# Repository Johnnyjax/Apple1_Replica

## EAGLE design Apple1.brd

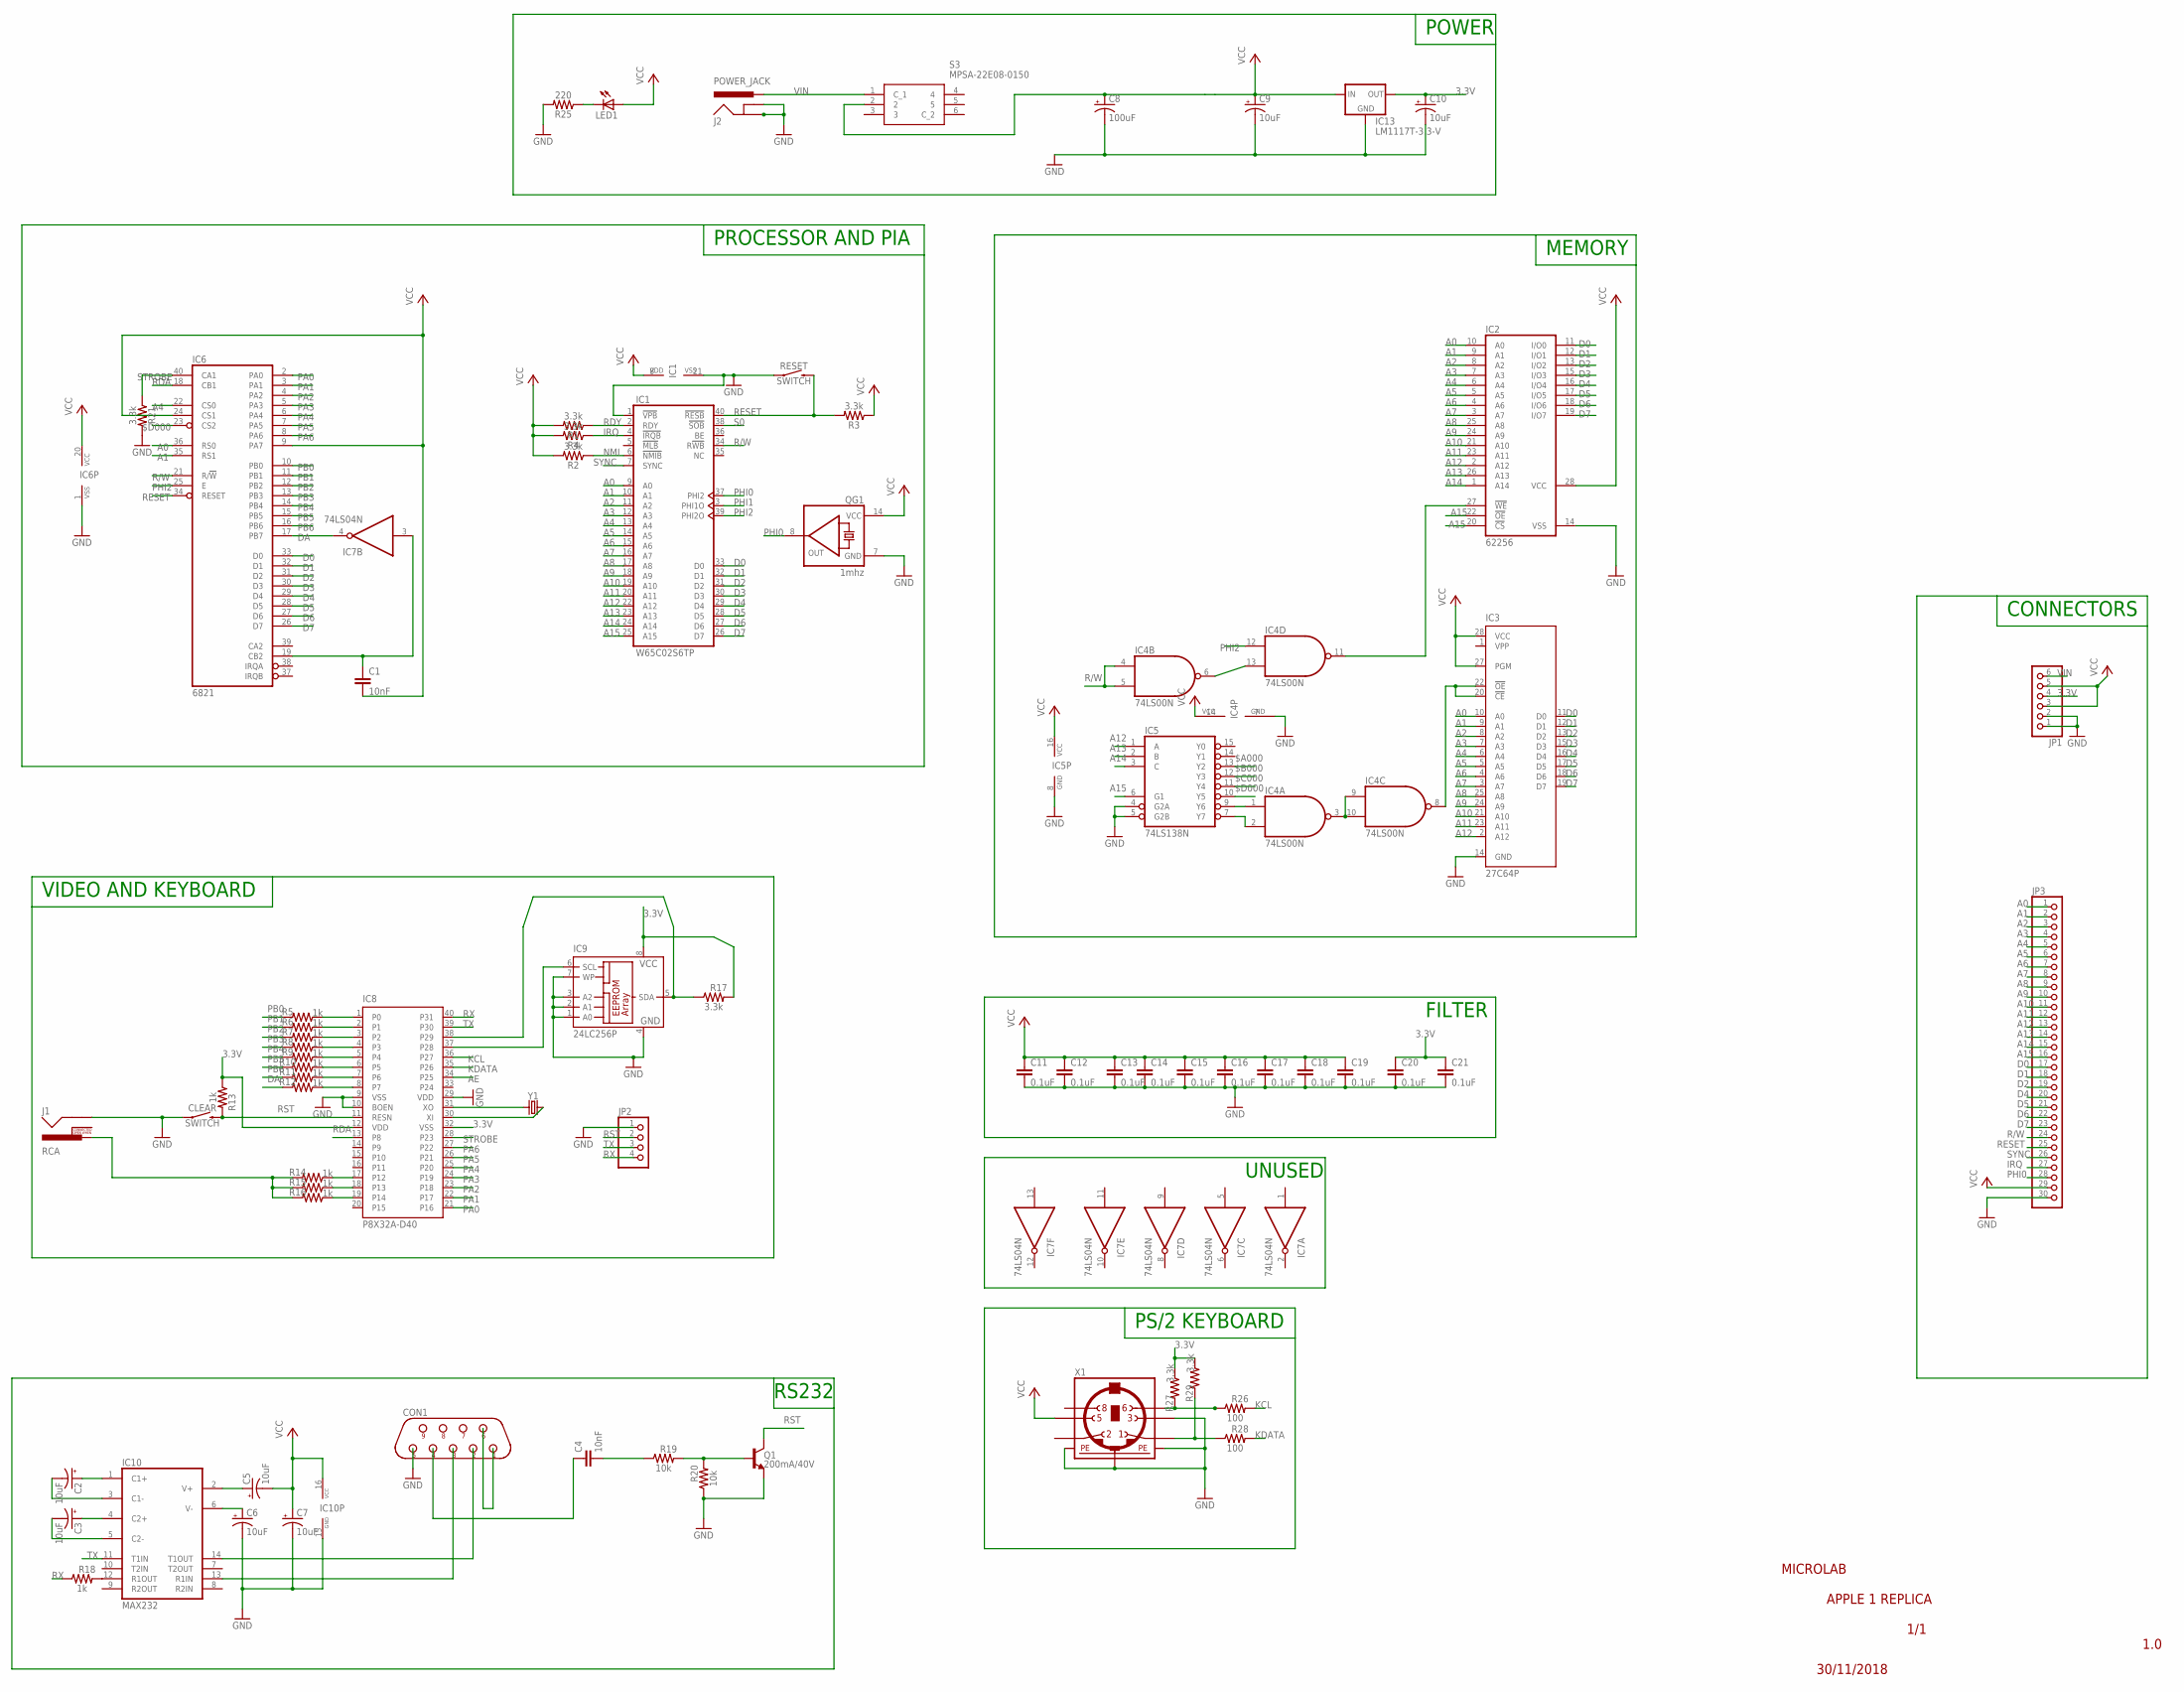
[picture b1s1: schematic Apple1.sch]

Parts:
C1, C4: 10nF; CAP-PTH-10MM
C2, C3, C5, C6, C7, C9, C10: 10uF; CPOL-RADIAL-2.5MM-5MM
C8: 100uF; CPOL-RADIAL-2.5MM-6.5MM
C11, C12, C13, C14, C15, C16, C17, C18, C19, C20, C21: 0.1uF; CAP-PTH-SMALL-KIT
CLEAR: SWITCH; TACTILE_SWITCH_PTH_6.0MM
CON1: DB9F; D-09F
IC1: W65C02S6TP; DIL40
IC2: 62256; DIL28-6
IC3: 27C64P; DIL28-6
IC4: 74LS00N; DIL14
IC5: 74LS138N; DIL16
IC6: 6821; DIL40
IC7: 74LS04N; DIL14
IC8: P8X32A-D40; DIL40
IC9: 24LC256P; DIL8
IC10: MAX232; DIL16
IC13: LM1117T-3.3-V; TO220V
J1: RCA
J2: POWER_JACK; POWER_JACK_PTH
JP1: PINHD-1X6B; 1X06-BIG
JP2: PINHD-1X4; 1X04
JP3: PINHD-1X30; 1X30
LED1: LED5MM
Q1: 200mA/40V; TO-92
QG1: 1mhz; DIL14S
R1, R2, R3, R4, R17, R21, R27, R29: 3.3k; AXIAL-0.3
R5, R6, R7, R8, R9, R10, R11, R12, R13, R14, R15, R16, R18: 1k; AXIAL-0.3
R19, R20: 10k; AXIAL-0.3
R25: 220; AXIAL-0.3
R26, R28: 100; AXIAL-0.3
RESET: SWITCH; TACTILE_SWITCH_PTH_6.0MM
S3: MPSA-22E08-0150; MPSA22E080150
X1: MINI_DIN_6; M_DIN6
Y1: CRYSTALPTH-HC49UV; HC49U

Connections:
3.3V: C10.1 (+), C20.1, C21.1, IC8.12 (VDD), IC8.32 (VSS), IC9.8 (VCC), IC13.2 (OUT), JP1.4, R13.P$1 (1), R17.P$2 (2), R27.P$1 (1), R29.P$1 (1)
$A000: IC5.13 (Y2)
$B000: IC5.12 (Y3)
$C000: IC5.11 (Y4)
$D000: IC5.10 (Y5), IC6.23 (CS2)
A0: IC1.9 (A0), IC2.10 (A0), IC3.10 (A0), IC6.36 (RS0), JP3.1
A1: IC1.10 (A1), IC2.9 (A1), IC3.9 (A1), IC6.35 (RS1), JP3.2
A2: IC1.11 (A2), IC2.8 (A2), IC3.8 (A2), JP3.3
A3: IC1.12 (A3), IC2.7 (A3), IC3.7 (A3), JP3.4
A4: IC1.13 (A4), IC2.6 (A4), IC3.6 (A4), IC6.22 (CS0), JP3.5
A5: IC1.14 (A5), IC2.5 (A5), IC3.5 (A5), JP3.6
A6: IC1.15 (A6), IC2.4 (A6), IC3.4 (A6), JP3.7
A7: IC1.16 (A7), IC2.3 (A7), IC3.3 (A7), JP3.8
A8: IC1.17 (A8), IC2.25 (A8), IC3.25 (A8), JP3.9
A9: IC1.18 (A9), IC2.24 (A9), IC3.24 (A9), JP3.10
A10: IC1.19 (A10), IC2.21 (A10), IC3.21 (A10), JP3.11
A11: IC1.20 (A11), IC2.23 (A11), IC3.23 (A11), JP3.12
A12: IC1.22 (A12), IC2.2 (A12), IC3.2 (A12), IC5.1 (A), JP3.13
A13: IC1.23 (A13), IC2.26 (A13), IC5.2 (B), JP3.14
A14: IC1.24 (A14), IC2.1 (A14), IC5.3 (C), JP3.15
A15: IC1.25 (A15), IC2.20 (!CS), IC2.22 (!OE), IC5.6 (G1), JP3.16
AE: IC8.34 (P25)
D0: IC1.33 (D0), IC2.11 (I/O0), IC3.11 (D0), IC6.33 (D0), JP3.17
D1: IC1.32 (D1), IC2.12 (I/O1), IC3.12 (D1), IC6.32 (D1), JP3.18
D2: IC1.31 (D2), IC2.13 (I/O2), IC3.13 (D2), IC6.31 (D2), JP3.19
D3: IC1.30 (D3), IC2.15 (I/O3), IC3.15 (D3), IC6.30 (D3)
D4: IC1.29 (D4), IC2.16 (I/O4), IC3.16 (D4), IC6.29 (D4), JP3.20
D5: IC1.28 (D5), IC2.17 (I/O5), IC3.17 (D5), IC6.28 (D5), JP3.21
D6: IC1.27 (D6), IC2.18 (I/O6), IC3.18 (D6), IC6.27 (D6), JP3.22
D7: IC1.26 (D7), IC2.19 (I/O7), IC3.19 (D7), IC6.26 (D7), JP3.23
DA: IC6.17 (PB7), IC7.4 (O), R12.P$2 (2)
GND: C6.2 (-), C7.2 (-), C8.2 (-), C9.2 (-), C10.2 (-), C11.2, C12.2, C13.2, C14.2, C15.2, C16.2, C17.2, C18.2, C19.2, C20.2, C21.2, CLEAR.1, CON1.5, IC1.1 (!VPB), IC1.21 (VSS), IC2.14 (VSS), IC3.14 (GND), IC4.7 (GND), IC5.4 (G2A), IC5.5 (G2B), IC5.8 (GND), IC6.1 (VSS), IC7.7 (GND), IC8.9 (VSS), IC8.10 (BOEN), IC8.29 (VDD), IC9.1 (A0), IC9.2 (A1), IC9.3 (A2), IC9.4 (GND), IC9.7 (WP), IC10.15 (GND), IC13.1 (GND), J1.SHELL, J2.GND, J2.GNDBREAK, JP1.1, JP1.2, JP2.1, JP3.30, Q1.1 (E), QG1.7 (GND), R20.P$1 (1), R21.P$2 (2), R25.P$2 (2), RESET.1, X1.3, X1.SH1 (PE1), X1.SH2 (PE2), X1.SH3 (PE3)
IRQ: IC1.4 (!IRQB), JP3.27, R4.P$1 (1)
KCL: IC8.36 (P27), R26.P$2 (2)
KDATA: IC8.35 (P26), R28.P$2 (2)
unnamed: IC2.27 (!WE), IC4.11 (O)
unnamed: IC4.3 (O), IC4.9 (I0), IC4.10 (I1)
unnamed: IC3.20 (!CE), IC3.22 (!OE), IC4.8 (O)
unnamed: IC4.1 (I0), IC5.9 (Y6)
unnamed: IC4.2 (I1), IC5.7 (Y7)
unnamed: IC4.6 (O), IC4.13 (I1)
unnamed: C1.1, IC6.19 (CB2), IC7.3 (I)
unnamed: IC8.1 (P0), R5.P$1 (1)
unnamed: IC8.2 (P1), R6.P$1 (1)
unnamed: IC8.3 (P2), R7.P$1 (1)
unnamed: IC8.4 (P3), R8.P$1 (1)
unnamed: IC8.5 (P4), R9.P$1 (1)
unnamed: IC8.6 (P5), R10.P$1 (1)
unnamed: IC8.7 (P6), R11.P$1 (1)
unnamed: IC8.8 (P7), R12.P$1 (1)
unnamed: IC8.17 (P12), R14.P$1 (1)
unnamed: IC8.18 (P13), R15.P$1 (1)
unnamed: IC8.19 (P14), R16.P$1 (1)
unnamed: J1.PIN, R14.P$2 (2), R15.P$2 (2), R16.P$2 (2)
unnamed: IC8.31 (XO), Y1.1
unnamed: IC8.30 (XI), Y1.2
unnamed: IC10.12 (R1OUT), R18.P$2 (2)
unnamed: IC8.37 (P28), IC9.6 (SCL)
unnamed: IC8.38 (P29), IC9.5 (SDA), R17.P$1 (1)
unnamed: CON1.3, IC10.13 (R1IN)
unnamed: C2.1 (+), IC10.1 (C1+)
unnamed: C2.2 (-), IC10.3 (C1-)
unnamed: C3.1 (+), IC10.4 (C2+)
unnamed: C3.2 (-), IC10.5 (C2-)
unnamed: CON1.2, IC10.14 (T1OUT)
unnamed: CON1.1, CON1.6
unnamed: C4.1, CON1.4
unnamed: C4.2, R19.P$1 (1)
unnamed: Q1.2 (B), R19.P$2 (2), R20.P$2 (2)
unnamed: C5.1 (+), IC10.2 (V+)
unnamed: C6.1 (+), IC10.6 (V-)
unnamed: LED1.K (C), R25.P$1 (1)
unnamed: R26.P$1 (1), R27.P$2 (2), X1.6
unnamed: R28.P$1 (1), R29.P$2 (2), X1.1
NMI: IC1.6 (!NMIB), R2.P$1 (1)
PA0: IC6.2 (PA0), IC8.21 (P16)
PA1: IC6.3 (PA1), IC8.22 (P17)
PA2: IC6.4 (PA2), IC8.23 (P18)
PA3: IC6.5 (PA3), IC8.24 (P19)
PA4: IC6.6 (PA4), IC8.25 (P20)
PA5: IC6.7 (PA5), IC8.26 (P21)
PA6: IC6.8 (PA6), IC8.27 (P22)
PB0: IC6.10 (PB0), R5.P$2 (2)
PB1: IC6.11 (PB1), R6.P$2 (2)
PB2: IC6.12 (PB2), R7.P$2 (2)
PB3: IC6.13 (PB3), R8.P$2 (2)
PB4: IC6.14 (PB4), R9.P$2 (2)
PB5: IC6.15 (PB5), R10.P$2 (2)
PB6: IC6.16 (PB6), R11.P$2 (2)
PHI0: IC1.37 (PHI2), JP3.28, QG1.8 (OUT)
PHI1: IC1.3 (PHI1O)
PHI2: IC1.39 (PHI2O), IC4.12 (I0), IC6.25 (E)
R/W: IC1.34 (R!WB), IC4.4 (I0), IC4.5 (I1), IC6.21 (R/!W), JP3.24
RDA: IC6.18 (CB1), IC8.13 (P8)
RDY: IC1.2 (RDY), R1.P$1 (1)
RESET: IC1.40 (!RESB), IC6.34 (RESET), JP3.25, R3.P$2 (2), RESET.3 (2)
RST: CLEAR.3 (2), IC8.11 (RESN), JP2.2, Q1.3 (C), R13.P$2 (2)
RX: IC8.40 (P31), JP2.4, R18.P$1 (1)
S0: IC1.38 (!SOB)
STROBE: IC6.40 (CA1), IC8.28 (P23), R21.P$1 (1)
SYNC: IC1.7 (SYNC), JP3.26
TX: IC8.39 (P30), IC10.11 (T1IN), JP2.3
VCC: C1.2, C5.2 (-), C7.1 (+), C8.1 (+), C9.1 (+), C11.1, C12.1, C13.1, C14.1, C15.1, C16.1, C17.1, C18.1, C19.1, IC1.8 (VDD), IC2.28 (VCC), IC3.27 (PGM), IC3.28 (VCC), IC4.14 (VCC), IC5.16 (VCC), IC6.9 (PA7), IC6.20 (VCC), IC6.24 (CS1), IC7.14 (VCC), IC10.16 (VCC), IC13.3 (IN), JP1.3, JP1.5, JP3.29, LED1.A, QG1.14 (VCC), R1.P$2 (2), R2.P$2 (2), R3.P$1 (1), R4.P$2 (2), S3.2, X1.5
VIN: J2.PWR, JP1.6, S3.1 (C_1)

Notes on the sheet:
MEMORY
POWER
PROCESSOR AND PIA
VIDEO AND KEYBOARD
CONNECTORS
RS232
FILTER
PS/2 KEYBOARD
UNUSED
APPLE 1 REPLICA
1.0
30/11/2018
MICROLAB
1/1

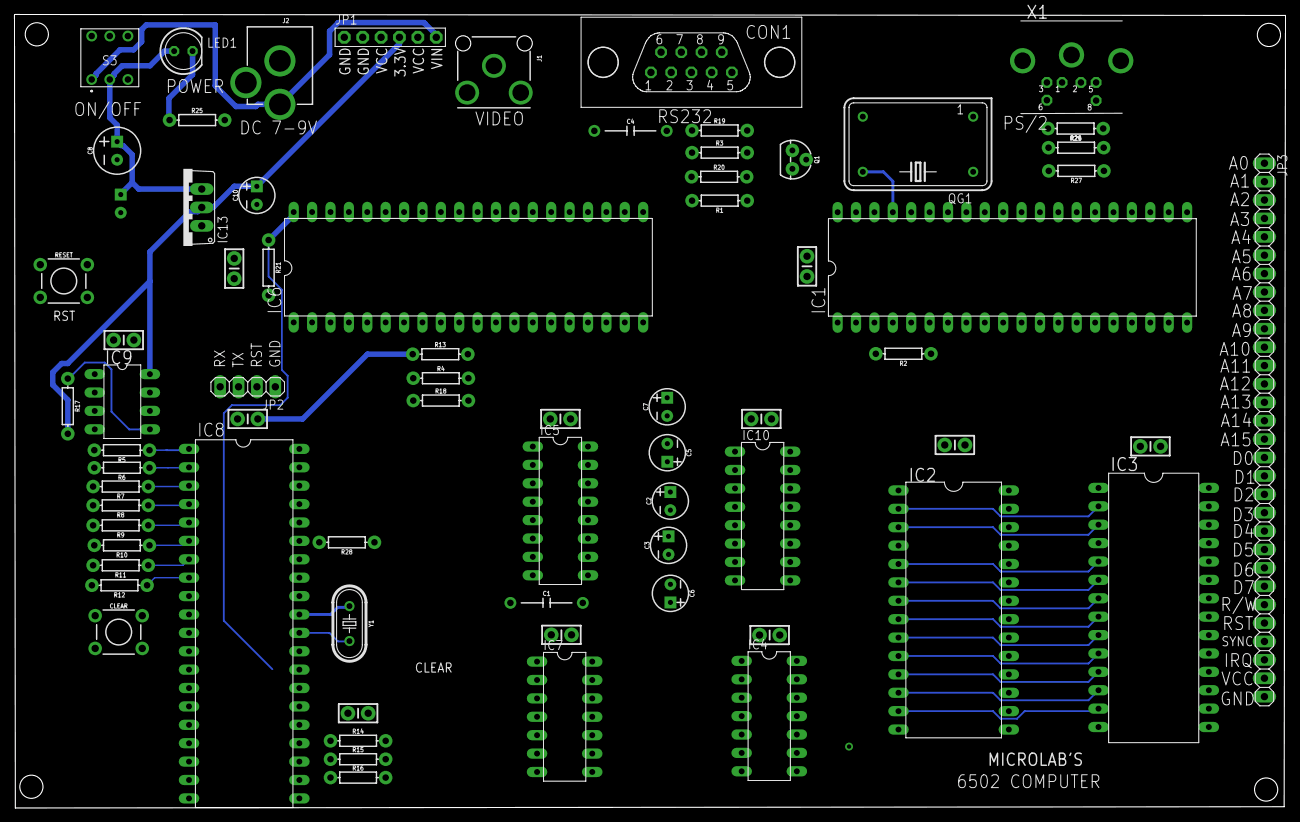
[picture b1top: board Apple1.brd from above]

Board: 2 copper layers, 175.5 x 109.6 mm, 72 parts (1 on the bottom side), 98 nets.

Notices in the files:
parts and their libraries:
SparkFun-Resistors: Licensing: Creative Commons ShareAlike 4.0 International - https://creativecommons.org/licenses/by-sa/4.0
